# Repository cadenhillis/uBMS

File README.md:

# uBMS
A tiny BMS to plug into things

I used this to plug into my uVU board, but it coulld be used for other things. A regular micro-B USB plugs in and charges it, and the little BMS chip and a boost supply do the rest for the 5V output.

I didn't get too long of a battery life from this into the uVU, but that isn't designed to be ultra low power anyways.

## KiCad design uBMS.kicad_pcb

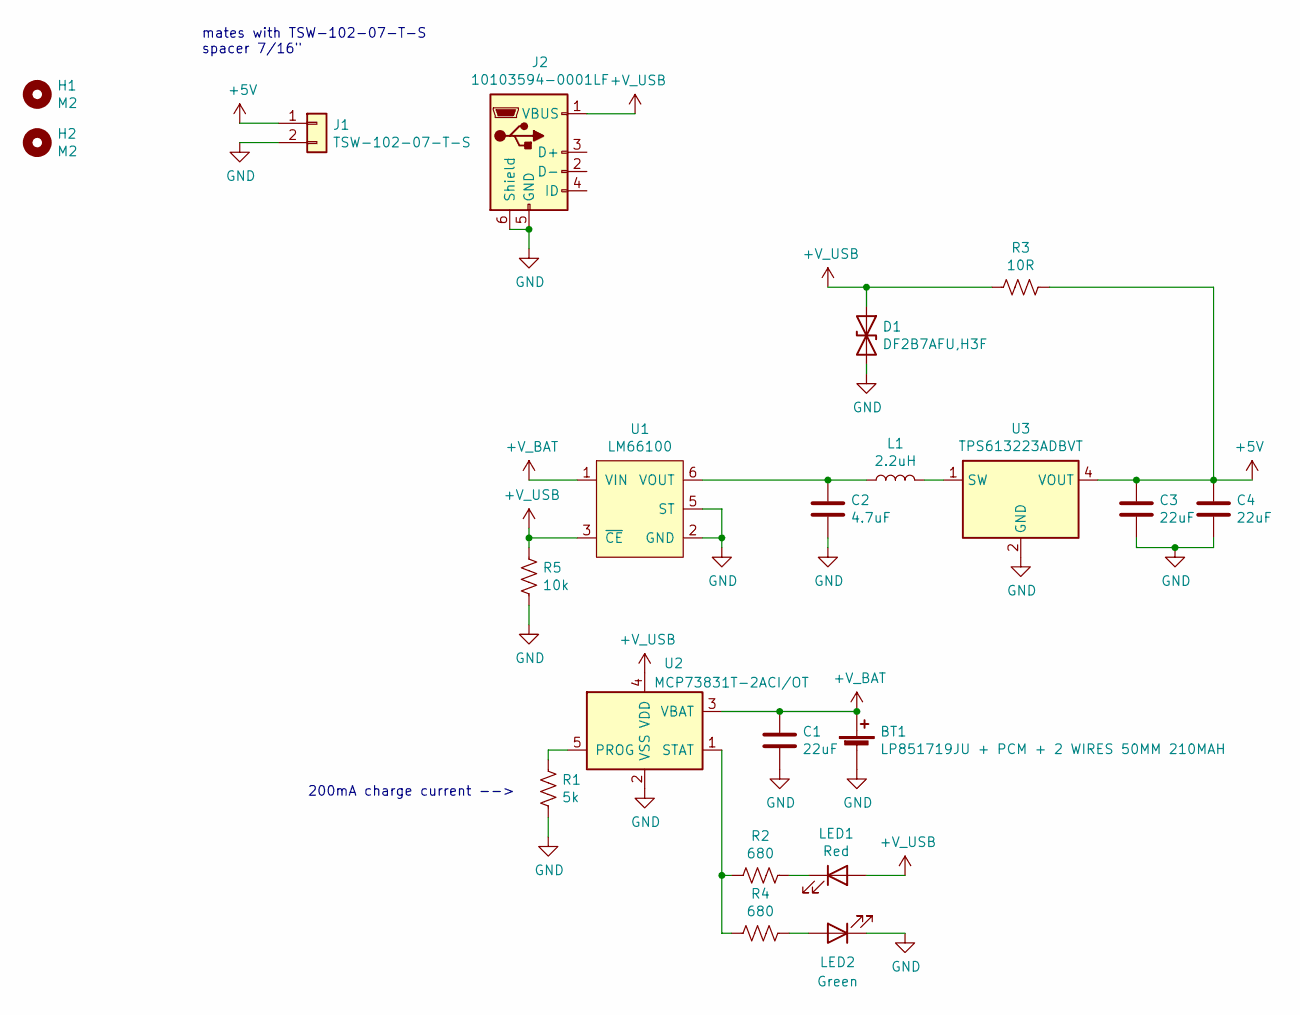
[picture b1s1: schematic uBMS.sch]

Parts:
BT1: LP851719JU + PCM + 2 WIRES 50MM 210MAH; LP851719JU
C1, C3, C4: 22uF; R_0805_2012Metric
C2: 4.7uF; C_0805_2012Metric
D1: DF2B7AFU,H3F; D_SOD-323_HandSoldering
H1, H2: M2; MountingHole_2.2mm_M2
J1: TSW-102-07-T-S; PinHeader_1x02_P2.54mm_Vertical
J2: 10103594-0001LF; USB_Micro-B_Amphenol_10103594-0001LF_Horizontal
L1: 2.2uH; L_Taiyo-Yuden_NR-24xx_HandSoldering
LED1: Red; LED_0603_1608Metric
LED2: Green; LED_0603_1608Metric
R1: 5k; R_0603_1608Metric
R2, R4: 680; R_0603_1608Metric
R3: 10R; R_0603_1608Metric
R5: 10k; R_0603_1608Metric
U1: LM66100; SC70-6
U2: MCP73831T-2ACI/OT; SOT-23-5
U3: TPS613223ADBVT; SOT-23-5

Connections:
+5V: C3.1, C4.1, J1.1, R3.1, U3.4 (VOUT)
+V_BAT: BT1.1 (+), C1.1, U1.1 (VIN), U2.3 (VBAT)
+V_USB: D1.1 (A1), J2.1 (VBUS), LED1.2 (A), R3.2, R5.1, U1.3 (~CE), U2.4 (VDD)
GND: BT1.2 (-), C1.2, C2.2, C3.2, C4.2, D1.2 (A2), J1.2, J2.5 (GND), J2.6 (Shield), LED2.1 (K), R1.2, R5.2, U1.2 (GND), U1.5 (ST), U2.2 (VSS), U3.2 (GND)
unnamed: C2.1, L1.1, U1.6 (VOUT)
unnamed: L1.2, U3.1 (SW)
unnamed: LED1.1 (K), R2.1
unnamed: LED2.2 (A), R4.1
unnamed: R1.1, U2.5 (PROG)
unnamed: R2.2, R4.2, U2.1 (STAT)

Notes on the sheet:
200mA charge current -->
mates with TSW-102-07-T-S spacer 7/16"

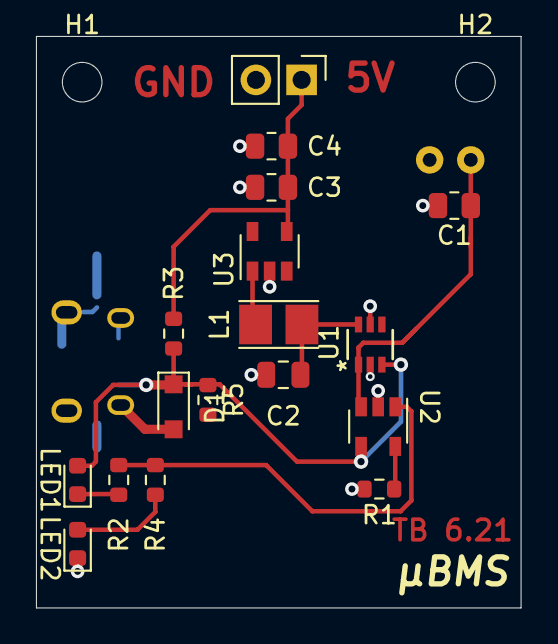
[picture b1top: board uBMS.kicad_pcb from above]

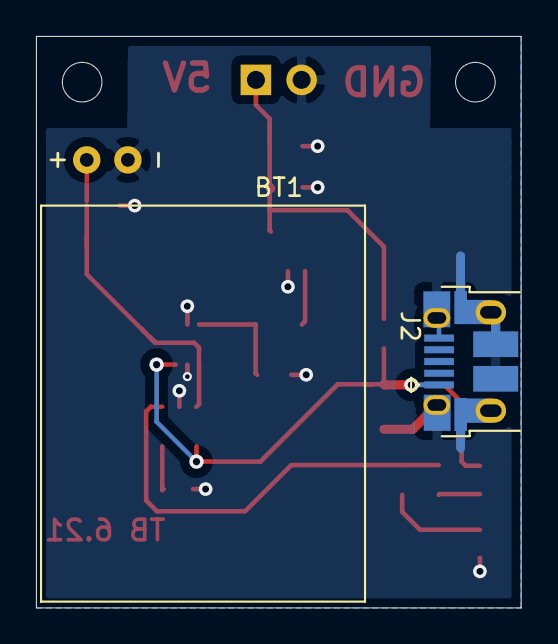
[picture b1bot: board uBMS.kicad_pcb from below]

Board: 2 copper layers, 26.9 x 31.8 mm, 21 parts (2 on the bottom side), 10 nets.

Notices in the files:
parts and their libraries:
Copyright 2016 Accelerated Designs. All rights reserved.
